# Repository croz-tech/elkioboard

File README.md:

# elkioboard
I/O board for Acorn Electron (with user port cart) or BBC Micro range

Compatible with many 8-bit robot or control projects. Inputs are for switches (switches from input to +5V), Outputs drive relays.
|Bit  |Alloc     |Details                                               |
|-----|----------|------------------------------------------------------|
|PB0  | Out only | DPDT relay (can be configured to reverse a motor drive)|
|PB1  | Out only | SPDT relay|
|PB2  | In/Out   | Input switched to +5V  / SPDT relay (selectable by JP1)|
|PB3  | In/Out   | Input switched to +5V  / SPDT relay (selectable by JP2)|
|PB4  | In/Out   | Input switched to +5V  / SPDT relay (selectable by JP3)|
|PB5  | In/Out   | Input switched to +5V  / SPDT relay (selectable by JP4)|
|PB6  | In only  | Input switched to +5V|
|PB7  | In only  | Input switched to +5V|

Includes a local 5V supply (since the total load with all specified relays energized may be too much for the user port itself, and generates an adjustable MOTPWR supply for motors, solenoids etc that the system is driving.  MOTPWR can be monitored with a small DVM module (3-pin header provided).  There is also a header and power/ground for CB1/CB2 from the user port (not used on this board).

## Notes
- Remember the base address for the 6522 PIA is &FE6x BBC Micro and &FCBx Electron with user port cartiridge in a Plus 1
- RV1 needs to be 5x5mm pin spacing, specified as 500R but 1K also works just fine and gives an adjustable motor supply of 2.5~9V approx.

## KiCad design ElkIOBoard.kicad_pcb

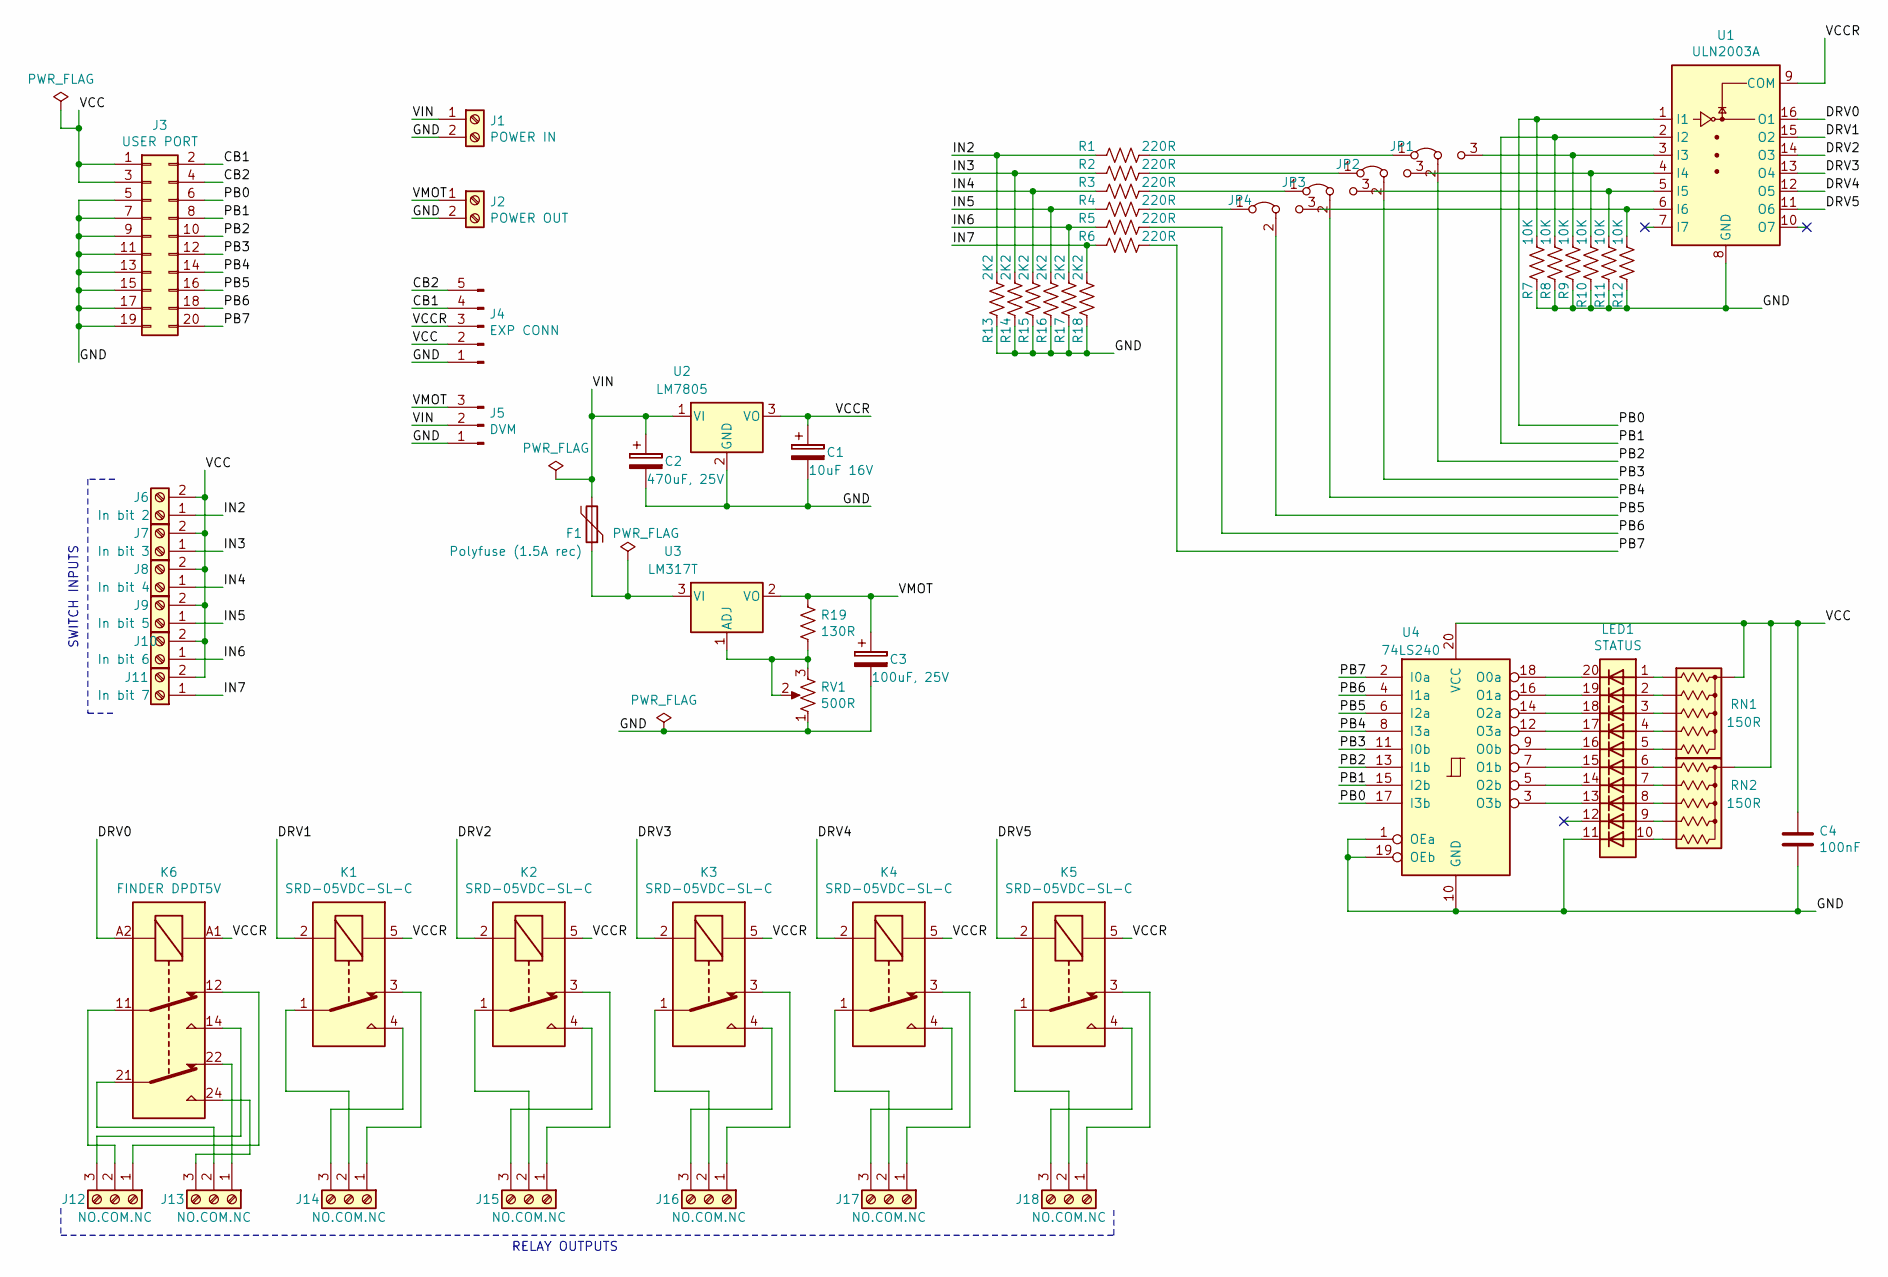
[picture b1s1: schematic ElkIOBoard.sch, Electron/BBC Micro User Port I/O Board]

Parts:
C1: 10uF 16V; CP_Radial_D5.0mm_P2.00mm
C2: 470uF, 25V; CP_Radial_D10.0mm_P5.00mm
C3: 100uF, 25V; CP_Radial_D6.3mm_P2.50mm
C4: 100nF; C_Rect_L7.0mm_W2.5mm_P5.00mm
F1: Polyfuse (1.5A rec); C_Disc_D10.5mm_W5.0mm_P5.00mm
J1: POWER IN; TerminalBlock_Philmore_TB132_1x02_P5.00mm_Horizontal
J2: POWER OUT; TerminalBlock_Philmore_TB132_1x02_P5.00mm_Horizontal
J3: USER PORT; 20W_IDC_TERM
J4: EXP CONN; PinHeader_1x05_P2.54mm_Vertical
J5: DVM; PinHeader_1x03_P2.54mm_Vertical
J6: In bit 2; TerminalBlock_Philmore_TB132_1x02_P5.00mm_Horizontal
J7: In bit 3; TerminalBlock_Philmore_TB132_1x02_P5.00mm_Horizontal
J8: In bit 4; TerminalBlock_Philmore_TB132_1x02_P5.00mm_Horizontal
J9: In bit 5; TerminalBlock_Philmore_TB132_1x02_P5.00mm_Horizontal
J10: In bit 6; TerminalBlock_Philmore_TB132_1x02_P5.00mm_Horizontal
J11: In bit 7; TerminalBlock_Philmore_TB132_1x02_P5.00mm_Horizontal
J12, J13, J14, J15, J16, J17, J18: NO.COM.NC; TerminalBlock_Philmore_TB133_1x03_P5.00mm_Horizontal
JP1, JP2, JP3, JP4: Jumper_3_Bridged12; PinHeader_1x03_P2.54mm_Vertical
K1, K2, K3, K4, K5: SRD-05VDC-SL-C; Relay_SPDT_SANYOU_SRD_Series_Form_C
K6: FINDER DPDT5V; Relay_DPDT_Finder_30.22
LED1: STATUS; HDSP-4830
R1, R2, R3, R4, R5, R6: 220R; R_Axial_DIN0207_L6.3mm_D2.5mm_P10.16mm_Horizontal
R7, R8, R9, R10, R11, R12: 10K; R_Axial_DIN0207_L6.3mm_D2.5mm_P10.16mm_Horizontal
R13, R14, R15, R16, R17, R18: 2K2; R_Axial_DIN0207_L6.3mm_D2.5mm_P10.16mm_Horizontal
R19: 130R; R_Axial_DIN0207_L6.3mm_D2.5mm_P10.16mm_Horizontal
RN1, RN2: 150R; R_Array_SIP6
RV1: 500R; Potentiometer_Piher_PT-10-V05_Vertical
U1: ULN2003A; DIP-16_W7.62mm_LongPads
U2: LM7805; TO-220-3_Horizontal_TabDown
U3: LM317T; TO-220-3_Horizontal_TabDown
U4: 74LS240; DIP-20_W7.62mm_LongPads

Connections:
/CB1: J3.2, J4.4
/CB2: J3.4, J4.5
/DRV0: K6.A2, U1.16 (O1)
/DRV1: K1.2, U1.15 (O2)
/DRV2: K2.2, U1.14 (O3)
/DRV3: K3.2, U1.13 (O4)
/DRV4: K4.2, U1.12 (O5)
/DRV5: K5.2, U1.11 (O6)
/GND: C1.2, C2.2, C3.2, C4.2, J1.2, J2.2, J3.5, J3.7, J3.9, J3.11, J3.13, J3.15, J3.17, J3.19, J4.1, J5.1, LED1.11 (K), R7.1, R8.1, R9.1, R10.1, R11.1, R12.1, R13.2, R14.2, R15.2, R16.2, R17.2, R18.2, RV1.1, U1.8 (GND), U2.2 (GND), U4.1 (OEa), U4.10 (GND), U4.19 (OEb)
/IN2: J6.1, R1.2, R13.1
/IN3: J7.1, R2.2, R14.1
/IN4: J8.1, R3.2, R15.1
/IN5: J9.1, R4.2, R16.1
/IN6: J10.1, R5.2, R17.1
/IN7: J11.1, R6.2, R18.1
/PB0: J3.6, R7.2, U1.1 (I1), U4.17 (I3b)
/PB1: J3.8, R8.2, U1.2 (I2), U4.15 (I2b)
/PB2: J3.10, JP1.2 (C), U4.13 (I1b)
/PB3: J3.12, JP2.2 (C), U4.11 (I0b)
/PB4: J3.14, JP3.2 (C), U4.8 (I3a)
/PB5: J3.16, JP4.2 (C), U4.6 (I2a)
/PB6: J3.18, R5.1, U4.4 (I1a)
/PB7: J3.20, R6.1, U4.2 (I0a)
/VCC: C4.1, J3.1, J3.3, J4.2, J6.2, J7.2, J8.2, J9.2, J10.2, J11.2, RN1.1 (common), RN2.1 (common), U4.20 (VCC)
/VCCR: C1.1, J4.3, K1.5, K2.5, K3.5, K4.5, K5.5, K6.A1, U1.9 (COM), U2.3 (VO)
/VIN: C2.1, F1.2, J1.1, J5.2, U2.1 (VI)
/VMOT: C3.1, J2.1, J5.3, R19.1, U3.2 (VO)
unnamed: F1.1, U3.3 (VI)
unnamed: J12.1, K6.12
unnamed: J12.2, K6.11
unnamed: J12.3, K6.14
unnamed: J13.1, K6.22
unnamed: J13.2, K6.21
unnamed: J13.3, K6.24
unnamed: J14.1, K1.3
unnamed: J14.2, K1.1
unnamed: J14.3, K1.4
unnamed: J15.1, K2.3
unnamed: J15.2, K2.1
unnamed: J15.3, K2.4
unnamed: J16.1, K3.3
unnamed: J16.2, K3.1
unnamed: J16.3, K3.4
unnamed: J17.1, K4.3
unnamed: J17.2, K4.1
unnamed: J17.3, K4.4
unnamed: J18.1, K5.3
unnamed: J18.2, K5.1
unnamed: J18.3, K5.4
unnamed: JP1.1 (A), R1.1
unnamed: JP1.3 (B), R9.2, U1.3 (I3)
unnamed: JP2.1 (A), R2.1
unnamed: JP2.3 (B), R10.2, U1.4 (I4)
unnamed: JP3.1 (A), R3.1
unnamed: JP3.3 (B), R11.2, U1.5 (I5)
unnamed: JP4.1 (A), R4.1
unnamed: JP4.3 (B), R12.2, U1.6 (I6)
unnamed: LED1.1 (A), RN1.2 (R1)
unnamed: LED1.2 (A), RN1.3 (R2)
unnamed: LED1.3 (A), RN1.4 (R3)
unnamed: LED1.4 (A), RN1.5 (R4)
unnamed: LED1.5 (A), RN1.6 (R5)
unnamed: LED1.6 (A), RN2.2 (R1)
unnamed: LED1.7 (A), RN2.3 (R2)
unnamed: LED1.8 (A), RN2.4 (R3)
unnamed: LED1.9 (A), RN2.5 (R4)
unnamed: LED1.10 (A), RN2.6 (R5)
unnamed: LED1.13 (K), U4.3 (O3b)
unnamed: LED1.14 (K), U4.5 (O2b)
unnamed: LED1.15 (K), U4.7 (O1b)
unnamed: LED1.16 (K), U4.9 (O0b)
unnamed: LED1.17 (K), U4.12 (O3a)
unnamed: LED1.18 (K), U4.14 (O2a)
unnamed: LED1.19 (K), U4.16 (O1a)
unnamed: LED1.20 (K), U4.18 (O0a)
unnamed: R19.2, RV1.2, RV1.3, U3.1 (ADJ)

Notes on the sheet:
RELAY OUTPUTS
SWITCH INPUTS

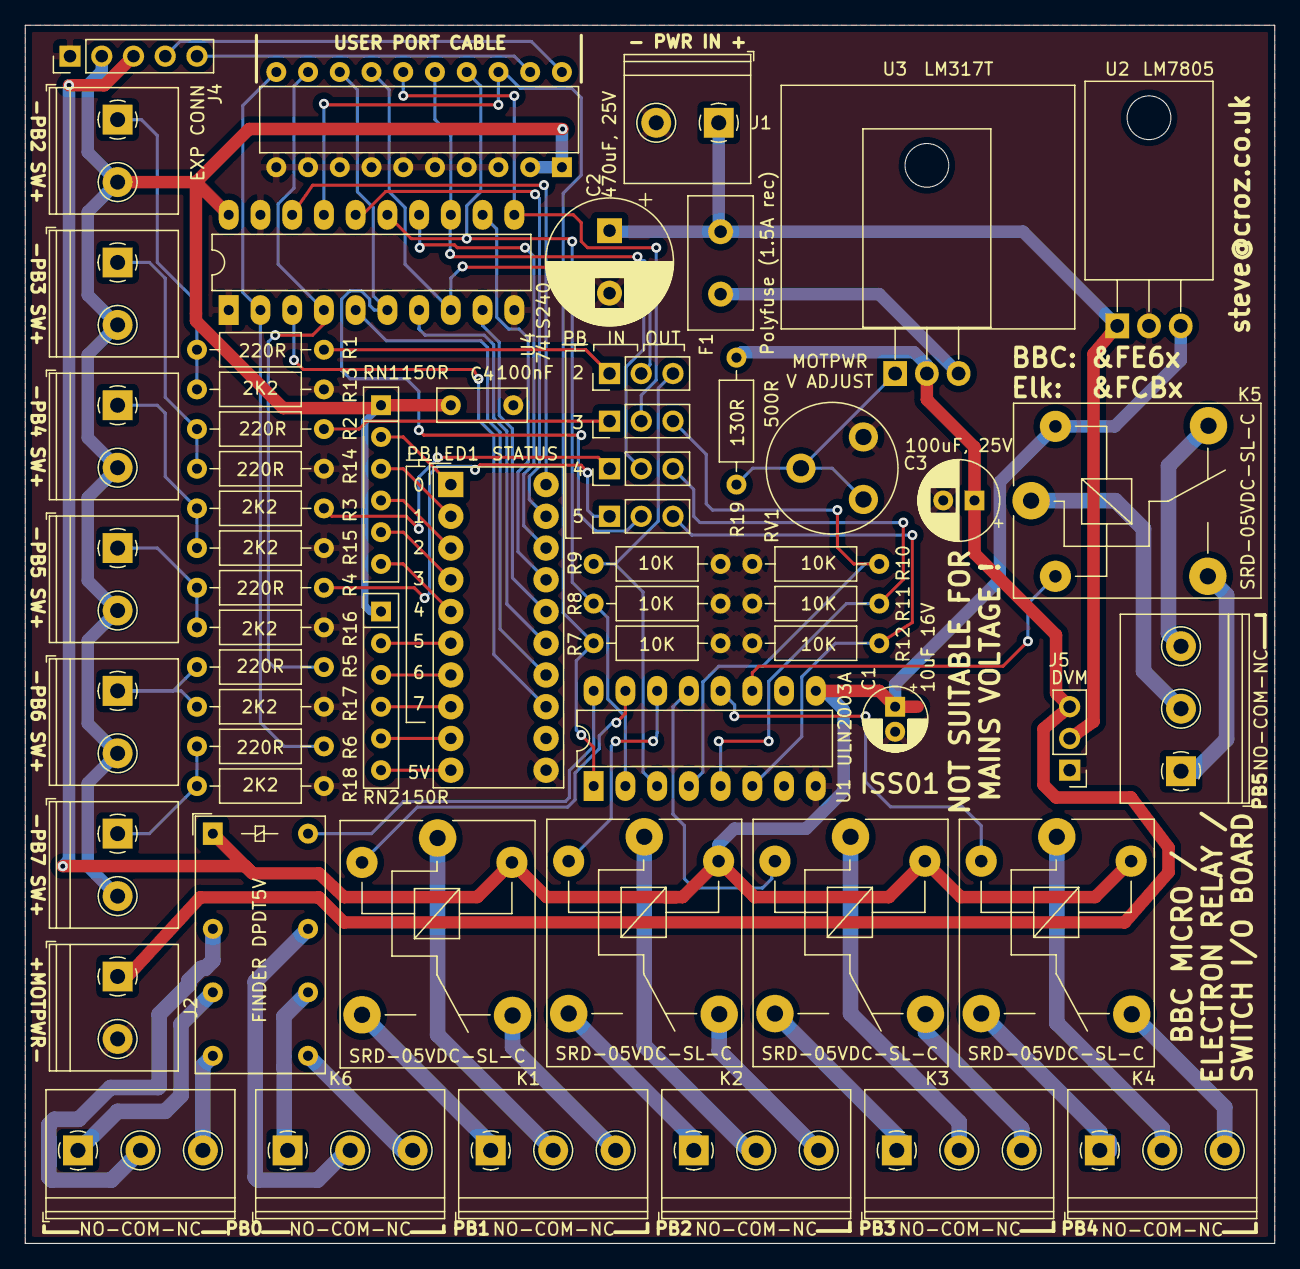
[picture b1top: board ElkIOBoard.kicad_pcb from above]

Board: 2 copper layers, 100.0 x 97.5 mm, 60 parts (0 on the bottom side), 76 nets.

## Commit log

2022-01-26 Add files via upload
    ISS01 design (untested)
